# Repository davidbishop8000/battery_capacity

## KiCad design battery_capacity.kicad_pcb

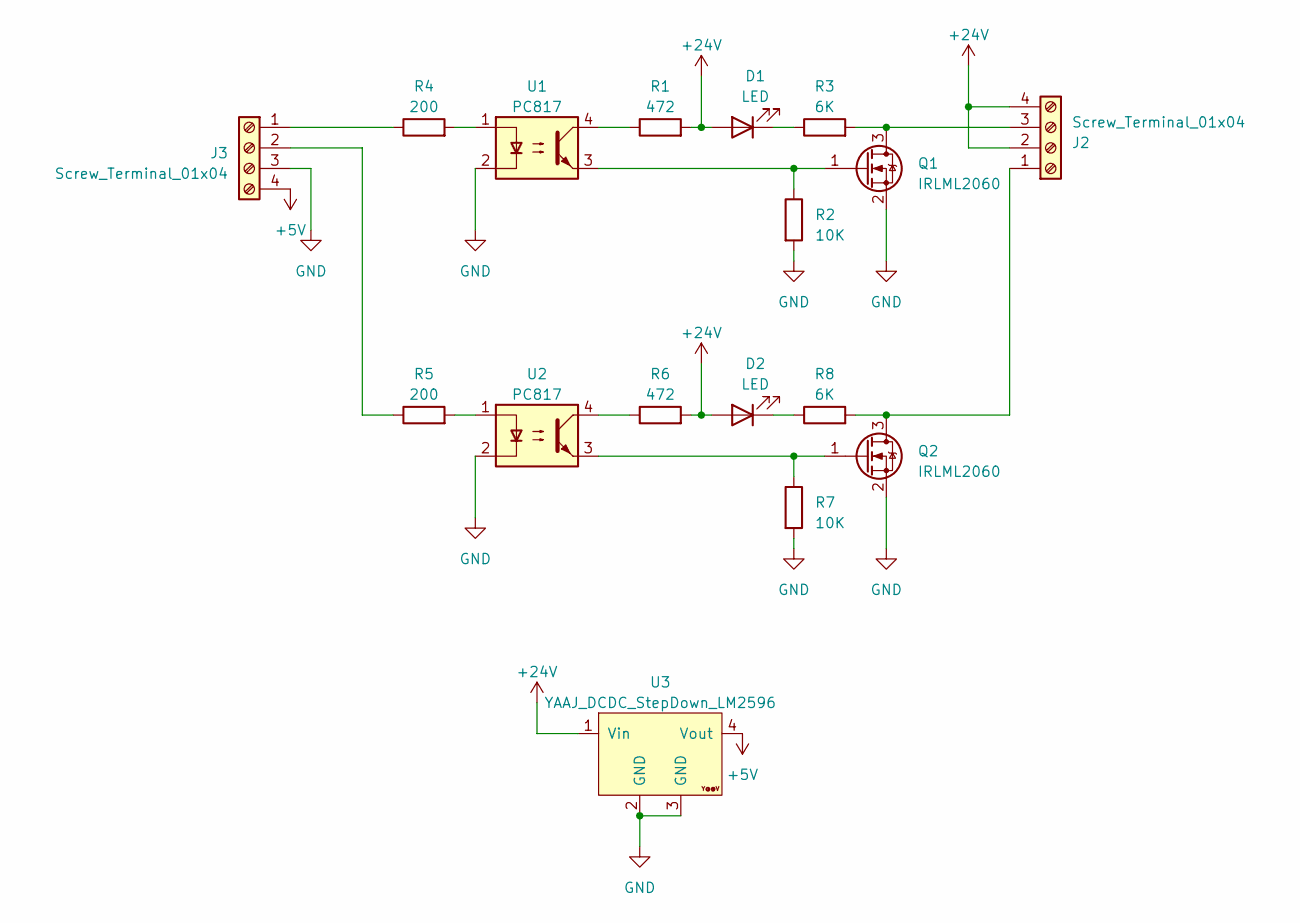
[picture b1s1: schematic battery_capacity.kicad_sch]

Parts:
D1, D2: LED; LED_D3.0mm
J2, J3: Screw_Terminal_01x04; Altech_AK300_1x04_P5.00mm_45-Degree
Q1, Q2: IRLML2060; SOT-23
R1, R6: 472; R_0805_2012Metric_Pad1.20x1.40mm_HandSolder
R2, R7: 10K; R_0805_2012Metric_Pad1.20x1.40mm_HandSolder
R3, R8: 6K; R_0805_2012Metric_Pad1.20x1.40mm_HandSolder
R4, R5: 200; R_0805_2012Metric_Pad1.20x1.40mm_HandSolder
U1, U2: PC817; DIP-4_W7.62mm
U3: YAAJ_DCDC_StepDown_LM2596; StepDown_LM2596

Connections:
+5V: J3.4, U3.4 (Vout)
+24V: D1.2 (A), D2.2 (A), J2.2, J2.4, R1.2, R6.2, U3.1 (Vin)
GND: J3.3, Q1.2 (S), Q2.2 (S), R2.2, R7.2, U1.2, U2.2, U3.2 (GND), U3.3 (GND)
unnamed: D1.1 (K), R3.1
unnamed: D2.1 (K), R8.1
unnamed: J2.1, Q2.3 (D), R8.2
unnamed: J2.3, Q1.3 (D), R3.2
unnamed: J3.1, R4.1
unnamed: J3.2, R5.1
unnamed: Q1.1 (G), R2.1, U1.3
unnamed: Q2.1 (G), R7.1, U2.3
unnamed: R1.1, U1.4
unnamed: R4.2, U1.1
unnamed: R5.2, U2.1
unnamed: R6.1, U2.4

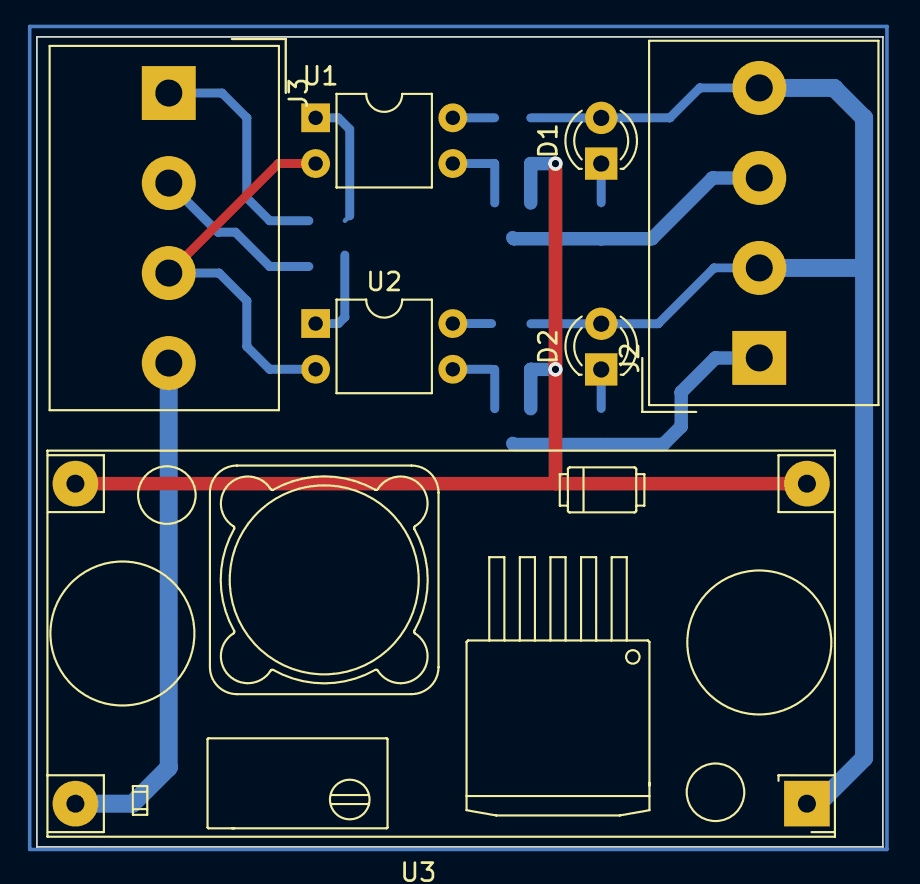
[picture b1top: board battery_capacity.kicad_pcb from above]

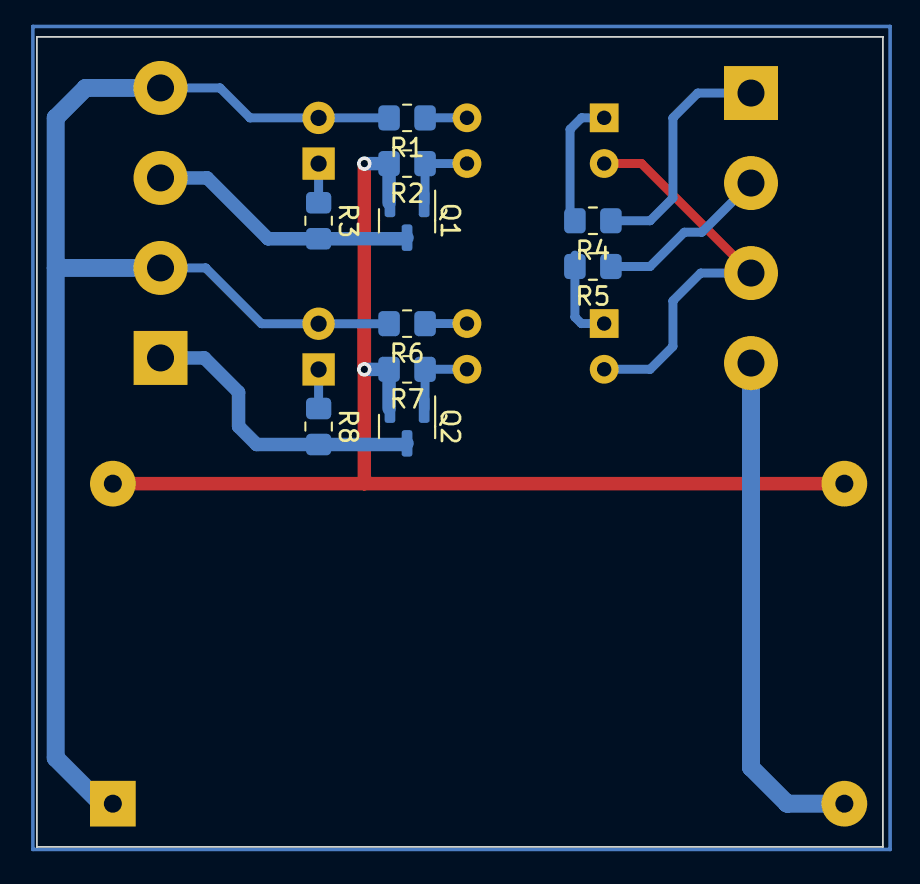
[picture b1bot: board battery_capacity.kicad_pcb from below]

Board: 2 copper layers, 47.0 x 45.0 mm, 17 parts (10 on the bottom side), 15 nets.
